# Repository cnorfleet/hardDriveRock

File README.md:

# Hard Drive Rock
Caleb and Erik's project for E155 (Microprocessor Systems) at Harvey Mudd College

A music player that creates sound by vibrating the reader heads inside of hard drives

Example video: https://www.cnorfleet.com/hardDriveMusicCarolOfTheBells.mp4

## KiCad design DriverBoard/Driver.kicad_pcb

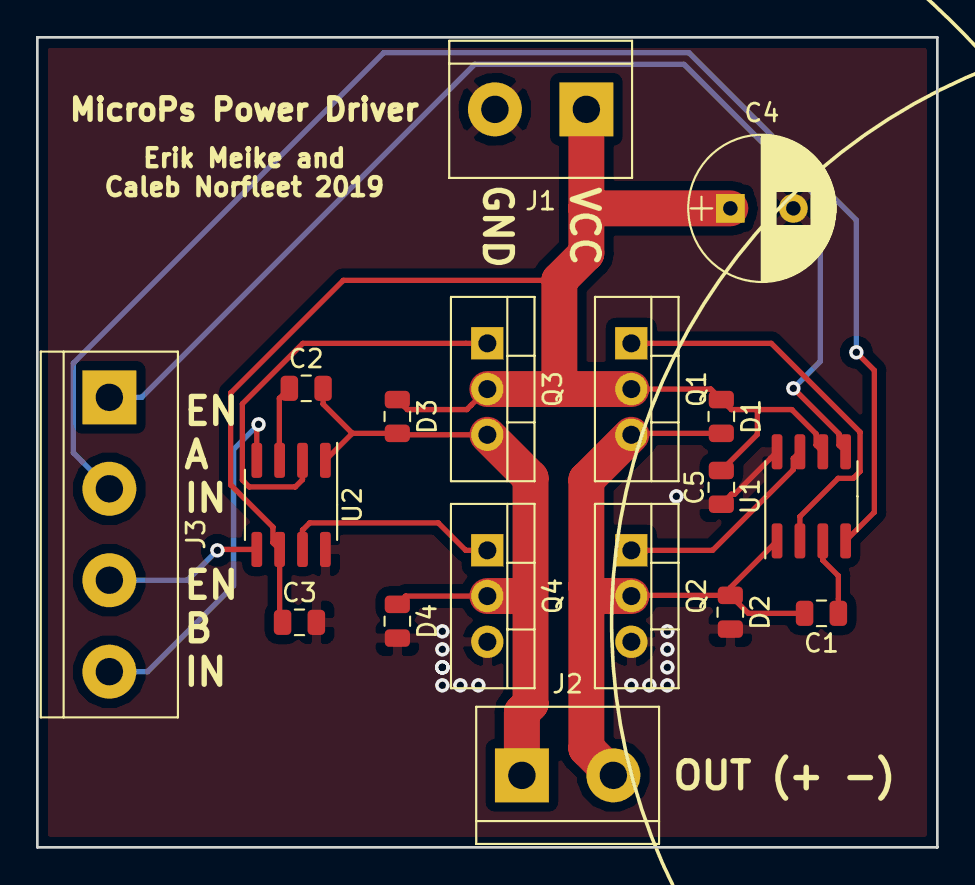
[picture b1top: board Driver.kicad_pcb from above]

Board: 2 copper layers, 50.0 x 45.0 mm, 18 parts (0 on the bottom side), 14 nets.

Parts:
C1, C2: 0.33uF; C_0805_2012Metric
C3, C5: 0.1uF; C_0805_2012Metric
C4: 100uF; CP_Radial_D8.0mm_P3.50mm
D1, D2, D3, D4: D_Shockley; C_0805_2012Metric
J1, J2: Screw_Terminal_01x02; TerminalBlock_bornier-2_P5.08mm
J3: Screw_Terminal_01x04; TerminalBlock_bornier-4_P5.08mm
Q1, Q2, Q3, Q4: IRF6623; TO-220-3_Vertical
U1, U2: LM27222; SOIC-8_3.9x4.9mm_P1.27mm

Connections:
/INA: J3.2, U1.4
/INB: J3.4, U2.4
/LENA: J3.1, U1.5
/LENB: J3.3, U2.5
/Out+: C2.2, D3.2, D4.1, J2.1, Q3.3, Q4.2, U2.1
/Out-: C1.2, D1.2, D2.1, J2.2, Q1.3, Q2.2, U1.1
GND: C3.2, C4.2, C5.2, D2.2, D4.2, J1.2, Q2.3, Q4.3, U1.8, U2.8
unnamed: C1.1, U1.3
unnamed: C2.1, U2.3
unnamed: Q1.1, U1.2
unnamed: Q2.1, U1.7
unnamed: Q3.1, U2.2
unnamed: Q4.1, U2.7
VCC: C3.1, C4.1, C5.1, D1.1, D3.1, J1.1, Q1.2, Q3.2, U1.6, U2.6

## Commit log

2019-11-15 add gitignore
2019-11-15 initial draft of spi implemented in verilog
2019-11-15 started adding top structure and began building cosine wave generator
2019-11-15 added sam code first draft
2019-11-15 added notes about pin numbers and stuff
2019-11-16 added python file for generating LUT and changed from freq to tuneWord in fpga
2019-11-16 switched to usine sin instead of cos and improved waveGen
2019-11-16 added pwmGen
2019-11-16 add testbench shell
2019-11-16 debug and now compiles
2019-11-16 pin planner for fpga complete with 3V3 lvttl
2019-11-17 minor:
2019-11-17 fixed delay between notes in sam code
2019-11-17 temp removed gitignore
2019-11-17 mess
2019-11-17 added testbench
2019-11-18 tesbench stuff
2019-11-18 debugged fpga stuff and now working with one output
2019-11-19 aaaaaa
2019-11-19 add more to gitignore
2019-11-19 got it to work yayayayayayay
2019-11-19 more debugging
2019-11-22 moved wgEn to pwmGen
2019-11-22 update gitignore
2019-11-22 gitignore
2019-11-22 clean up based on gitignore
2019-11-22 readd quartus project file
2019-11-22 improve structure of SPI and add watchdog timer
2019-11-22 improvements to SPI structure in fpga
2019-11-22 tuneWord now only changes at full wave points aka every other zero crossing such that zero frequency results in amplitude of zero
2019-11-22 playing around with adding midi songs
2019-11-25 started messing around with file upload to webpage
2019-11-29 minor fpga testbench updates and got things tested with new output module
2019-11-29 restructured webpage stuff and fixed bug with skipping rests at start
2019-11-29 fixed issue with stopping playing at end
2019-12-02 added songs for demo
2019-12-02 fixed watchdog and lots of improvements to output stage with all four fets
2019-12-02 added PCB
2019-12-02 minor
2019-12-09 updated sam code for using multiple tracks
2019-12-10 updated verilog and testbench for supporting multiple tracks
2019-12-10 implemented new outputGen with high and enable instead of ABCD
2019-12-10 cleaned up names with new output signals
2019-12-10 added lots of four track songs and a four track jic for the fpga
2019-12-11 got songs to play on finished 4 track setup
2019-12-11 auto pause at start and go to start paused at end of songs
2019-12-12 final version for demo with more songs
2019-12-25 minor stuff from projects day
2019-12-25 fixed bug with not playing first note at start of song
2020-01-17 add pulse density modulation module
2020-01-17 swapped numTracks and outputType to parameters instead of defines so that they can be better integrated with the testbench
2020-01-17 fixed parameter type for enum
2020-01-17 messing around with testbench stuff
2020-01-17 started adding funcitonality for visualizing low-pass filter of one-bit output in testbench
2020-01-17 got lowpass filter in testbench to work and also tried using the generate_block thing to select between pwm and pdm
2020-01-17 using generate_block was a total failure so switched to using compiler directives instead
2020-01-17 testing and wrapup of pdm and testbench functionality
2020-01-17 separated input tracks from output channels so that we can eventually have multiple tracks on each output and stuff
2020-01-17 fixed old bug with watchdog failing if last packet was incomplete
2020-01-17 testing out adding two input channels to make one output channe;
2020-01-17 fixed bug that caused phases near the edge of quarter phase table to sometimes read from the wrong spot
2020-05-08 add pcb image
2020-05-08 create pcb readme
2020-05-08 removed email addresses
